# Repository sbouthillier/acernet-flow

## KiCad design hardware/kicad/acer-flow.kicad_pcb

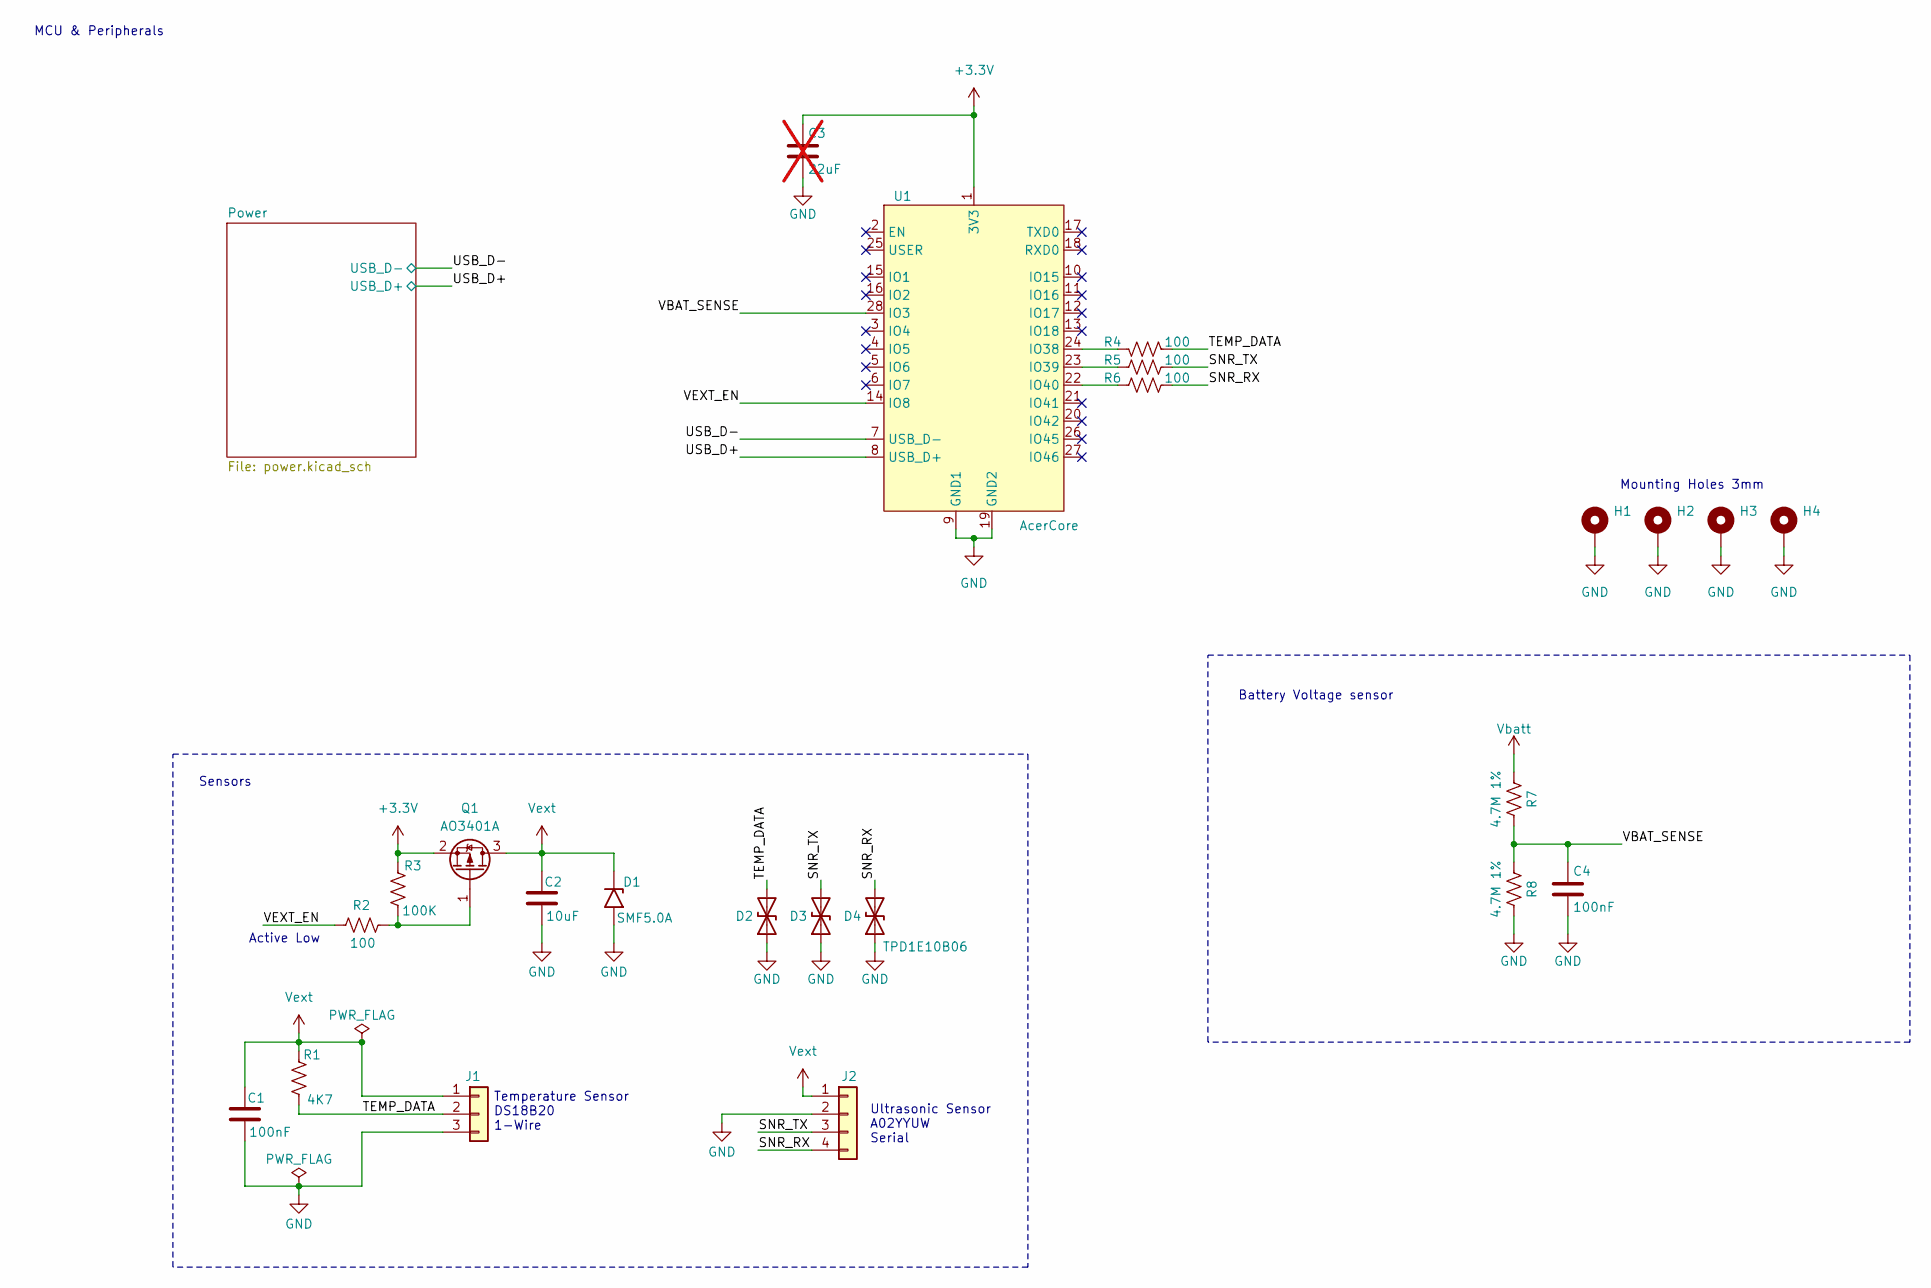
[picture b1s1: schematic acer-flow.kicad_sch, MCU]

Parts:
C1, C4: 100nF; C_0603_1608Metric; MPN CL10B104KB8WPNC
C2: 10uF; C_0603_1608Metric; MPN CL21A106KPFNNNG
C3: 22uF; C_0805_2012Metric; MPN CL21A226KPCLRNC; not fitted
D1: SMF5.0A; D_SOD-123F; MPN SMF5.0A
D2, D3, D4: TPD1E10B06; D_SOD-523; MPN TPD1E10B06DYAR
H1, H2, H3, H4: MountingHole_Pad; MountingHole_2.2mm_M2_ISO14580_Pad_TopBottom
J1: Conn_01x03; JST_XH_B3B-XH-A_1x03_P2.50mm_Vertical
J2: Conn_01x04; JST_XH_B4B-XH-A_1x04_P2.50mm_Vertical
Q1: AO3401A; SOT-23; MPN MMFTP3401-AQ
R1: 4K7; R_0603_1608Metric; MPN RC0603FR-074K7L
R2, R4, R5, R6: 100; R_0603_1608Metric; MPN RC0603FR-07100RL
R3: 100K; R_0603_1608Metric; MPN RC0603FR-07100KL
R7, R8: 4.7M 1%; R_0603_1608Metric; MPN RC0603FR-074M7L
U1: AcerCore

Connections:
+3.3V: C3.1, Q1.2 (S), R3.1, U1.1 (3V3); also elsewhere on the board
/SNR_RX: D4.2 (A2), J2.4, R6.2
/SNR_TX: D3.2 (A2), J2.3, R5.2
/TEMP_DATA: D2.2 (A2), J1.2, R1.2, R4.1
/USB_D+: U1.8 (USB_D+); also elsewhere on the board
/USB_D-: U1.7 (USB_D-); also elsewhere on the board
/VBAT_SENSE: C4.1, R7.2, R8.1, U1.28 (IO3)
/VEXT_EN: R2.1, U1.14 (IO8)
GND: C1.2, C2.2, C3.2, C4.2, D1.2 (A2), D2.1 (A1), D3.1 (A1), D4.1 (A1), H1.1 (1_1), H2.1 (1_1), H3.1 (1_1), H4.1 (1_1), J1.3, J2.2, R8.2, U1.9 (GND1), U1.19 (GND2); also elsewhere on the board
unnamed: Q1.1 (G), R2.2, R3.2
unnamed: R4.2, U1.24 (IO38)
unnamed: R5.1, U1.23 (IO39)
unnamed: R6.1, U1.22 (IO40)
Vbatt: R7.1; also elsewhere on the board
Vext: C1.1, C2.1, D1.1 (A1), J1.1, J2.1, Q1.3 (D), R1.1

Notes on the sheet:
Battery Voltage sensor
MCU & Peripherals
Mounting Holes 3mm
Active Low
Ultrasonic Sensor A02YYUW Serial
Sensors
Temperature Sensor DS18B20 1-Wire

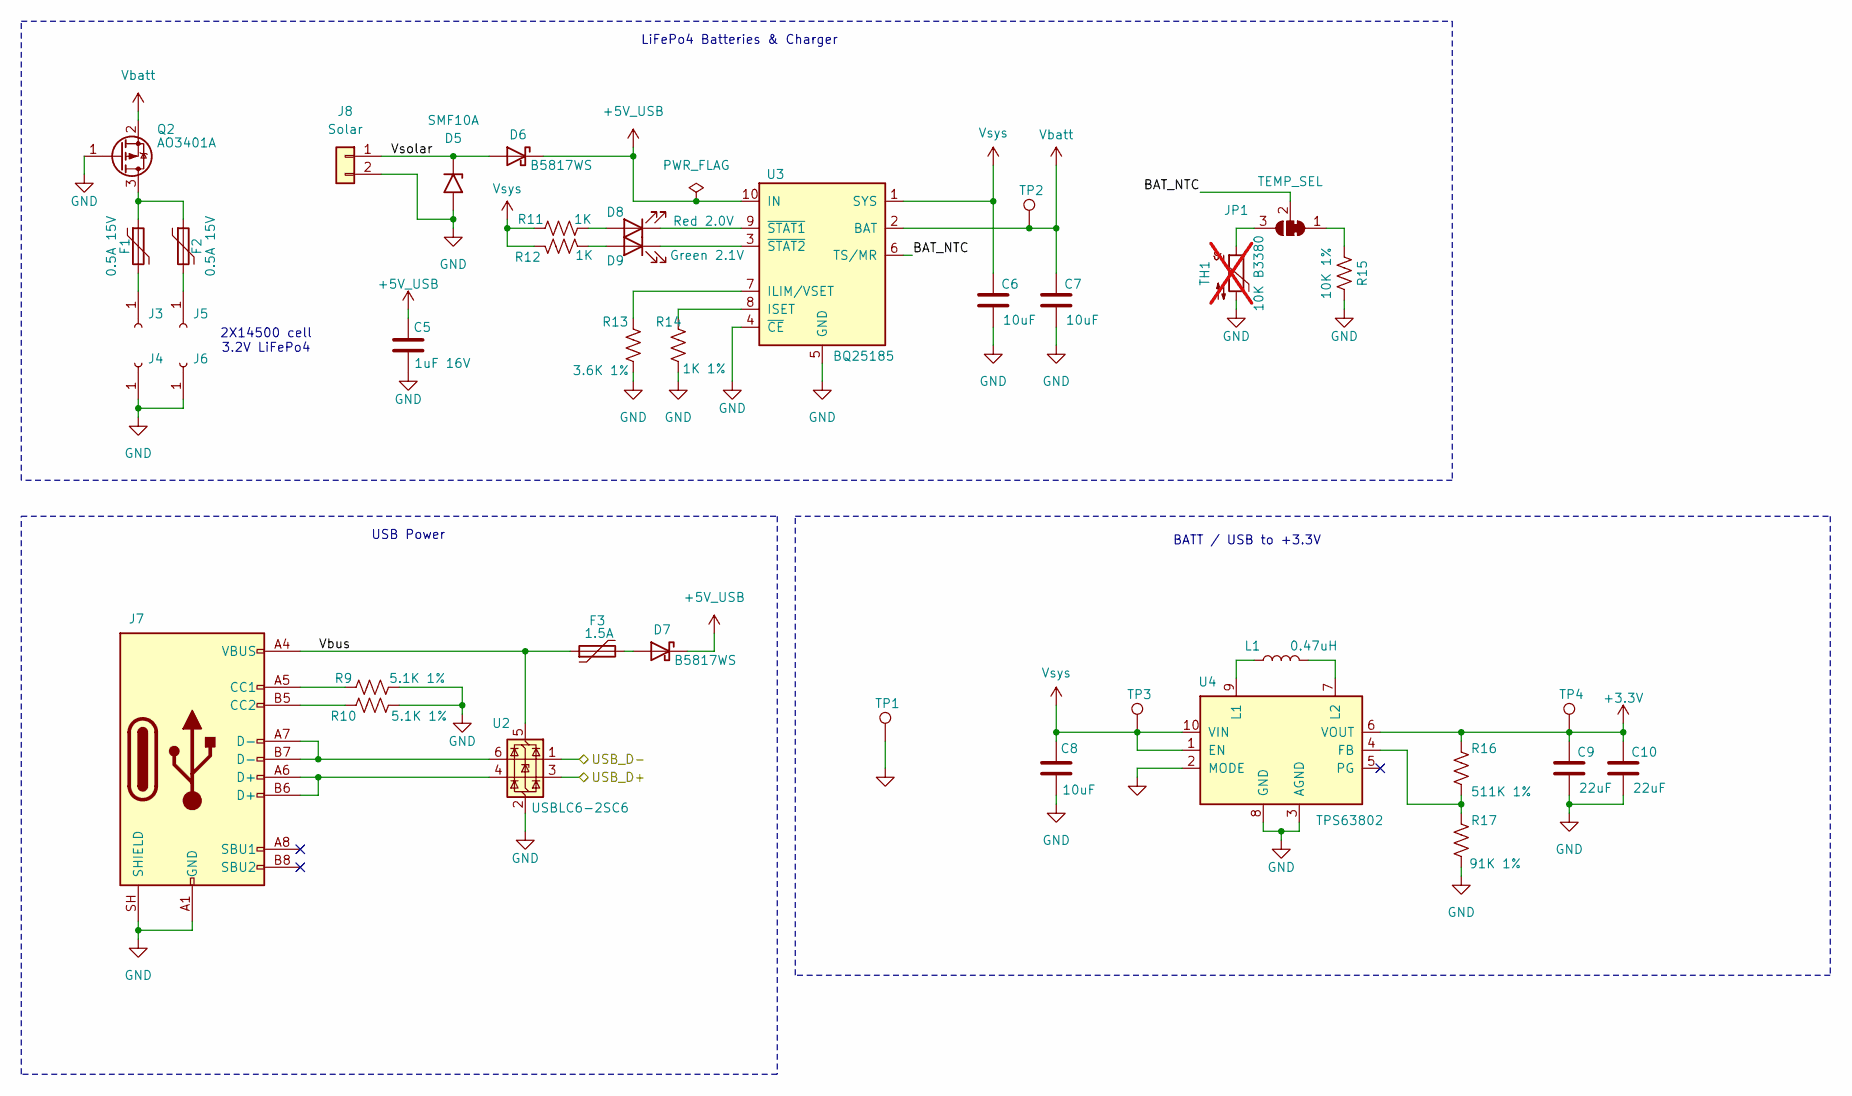
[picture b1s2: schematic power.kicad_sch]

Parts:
C5: 1uF 16V; C_0603_1608Metric; MPN CL10B105KO8VPNC
C6, C7, C8: 10uF; C_0603_1608Metric; MPN CL21A106KPFNNNG
C9, C10: 22uF; C_0805_2012Metric; MPN CL21A226KPCLRNC
D5: SMF10A; Nexperia_CFP3_SOD-123W; MPN SMF10A
D6, D7: B5817WS; D_SOD-323; MPN B5817WSHE3-TP
D8: Red 2.0V; LED_0603_1608Metric; MPN LTST-C190KRKT
D9: Green 2.1V; LED_0603_1608Metric; MPN LTST-C190GKT
F1, F2: 0.5A 15V; Fuse_1206_3216Metric; MPN 0ZCJ0050FF2G
F3: 1.5A; Fuse_1206_3216Metric; MPN 0ZCJ0150FF2C
J3, J4, J5, J6: Conn_01x01_Socket; BAT_BK-92; MPN BK-92
J7: USB_C_Receptacle_USB2.0_16P; UJ20-C-H-G-SMT-1-P16-TR; MPN UJ20-C-H-G-SMT-1-P16-TR
J8: Solar; JST_XH_B2B-XH-A_1x02_P2.50mm_Vertical
JP1: TEMP_SEL; SolderJumper-3_P1.3mm_Bridged12_RoundedPad1.0x1.5mm
L1: 0.47uH; L_Murata_DFE201610P; MPN DFE201612E-R47M=P2
Q2: AO3401A; SOT-23; MPN MMFTP3401-AQ
R9, R10: 5.1K 1%; R_0603_1608Metric; MPN RC0603FR-075K1L
R11, R12: 1K; R_0603_1608Metric; MPN RC0603FR-071KL
R13: 3.6K 1%; R_0603_1608Metric; MPN RC0603FR-073K6L
R14: 1K 1%; R_0603_1608Metric; MPN RC0603FR-071KL
R15: 10K 1%; R_0603_1608Metric; MPN RC0603FR-0710KL
R16: 511K 1%; R_0603_1608Metric; MPN RC0603FR-07511KL
R17: 91K 1%; R_0603_1608Metric; MPN RC0603FR-0791KL
TH1: 10K B3380; R_0603_1608Metric; MPN NCP18XH103F03RB; not fitted
TP1: GND; TestPoint_Pad_D1.5mm
TP2: Vbatt; TestPoint_Pad_D1.5mm
TP3: Vsys; TestPoint_Pad_D1.5mm
TP4: 3.3V; TestPoint_Pad_D1.5mm
U2: USBLC6-2SC6; SOT-23-6; MPN USBLC6-2SC6
U3: BQ25185; Texas_DLH0010A_WSON-10-1EP_2.2x2mm_P0.4mm_EP0.9x1.5mm_Therm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; MPN BQ25185DLHR
U4: TPS63802; VREG_TPS63802DLAR; MPN TPS63802DLAR

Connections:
+3.3V: C9.1, C10.1, R16.1, TP4.1, U4.6 (VOUT); also elsewhere on the board
+5V_USB: C5.1, D6.1 (K), D7.1 (K), U3.10 (IN)
/Power/BAT_NTC: JP1.2 (C), U3.6 (TS/MR)
/Power/Vbus: F3.1, J7.A4 (VBUS), J7.A9 (VBUS), J7.B4 (VBUS), J7.B9 (VBUS), U2.5 (VBUS)
/Power/Vsolar: D5.1 (A1), D6.2 (A), J8.1
/USB_D+: U2.3 (I/O2); also elsewhere on the board
/USB_D-: U2.1 (I/O1); also elsewhere on the board
GND: C5.2, C6.2, C7.2, C8.2, C9.2, C10.2, D5.2 (A2), J4.1 (Pin_1_1), J6.1 (Pin_1_1), J7.A1 (GND), J7.A12 (GND), J7.B1 (GND), J7.B12 (GND), J7.SH (SHIELD), J8.2, Q2.1 (G), R9.2, R10.2, R13.1, R14.2, R15.2, R17.2, TH1.2, TP1.1, U2.2 (GND), U3.4 (~CE), U3.5 (GND), U3.11 (EP), U4.2 (MODE), U4.3 (AGND), U4.8 (GND); also elsewhere on the board
unnamed: D7.2 (A), F3.2
unnamed: D8.2 (A), R11.2
unnamed: D8.1 (K), U3.9 (~STAT1)
unnamed: D9.2 (A), R12.2
unnamed: D9.1 (K), U3.3 (~STAT2)
unnamed: F1.2, J3.1 (Pin_1_1)
unnamed: F2.2, J5.1 (Pin_1_1)
unnamed: J7.A5 (CC1), R9.1
unnamed: J7.B5 (CC2), R10.1
unnamed: J7.A6 (D+), J7.B6 (D+), U2.4 (I/O2)
unnamed: J7.A7 (D-), J7.B7 (D-), U2.6 (I/O1)
unnamed: JP1.1 (A), R15.1
unnamed: JP1.3 (B), TH1.1
unnamed: F1.1, F2.1, Q2.3 (D)
unnamed: R13.2, U3.7 (ILIM/VSET)
unnamed: R14.1, U3.8 (ISET)
unnamed: R16.2, R17.1, U4.4 (FB)
unnamed: L1.1, U4.9 (L1)
unnamed: L1.2, U4.7 (L2)
Vbatt: C7.1, Q2.2 (S), TP2.1, U3.2 (BAT); also elsewhere on the board
Vsys: C6.1, C8.1, R11.1, R12.1, TP3.1, U3.1 (SYS), U4.1 (EN), U4.10 (VIN); also elsewhere on the board

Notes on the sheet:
BATT / USB to +3.3V
2X14500 cell 3.2V LiFePo4
LiFePo4 Batteries & Charger
USB Power

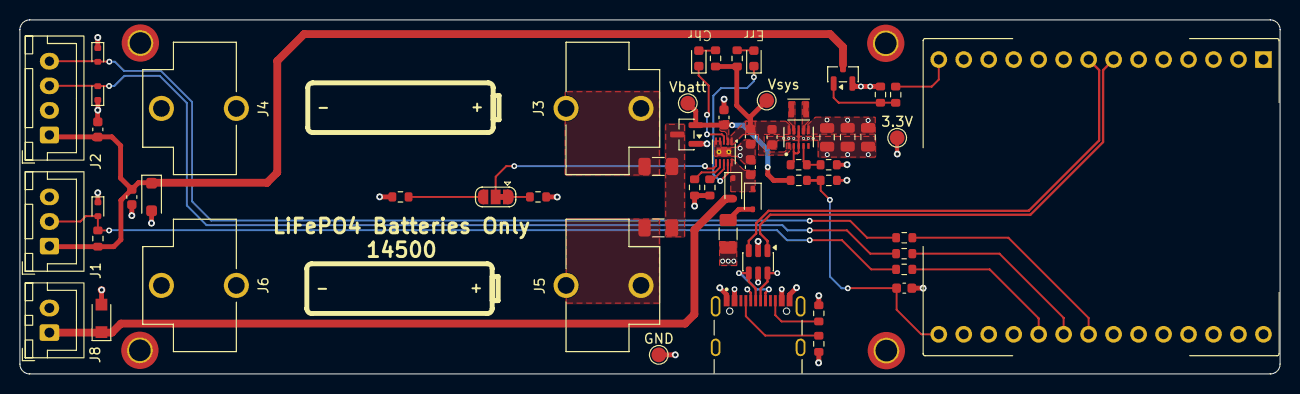
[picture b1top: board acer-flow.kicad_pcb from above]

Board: 4 copper layers, 128.1 x 36.0 mm, 64 parts (0 on the bottom side), 39 nets.

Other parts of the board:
3.3V: 3.3V; TestPoint_Pad_D1.5mm
GND: GND; TestPoint_Pad_D1.5mm
Vbatt: Vbatt; TestPoint_Pad_D1.5mm
Vsys: Vsys; TestPoint_Pad_D1.5mm

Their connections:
+3.3V: 3.3V.1 (1_1); also elsewhere on the board
GND: GND.1 (1_1); also elsewhere on the board
Vbatt: Vbatt.1 (1_1); also elsewhere on the board
Vsys: Vsys.1 (1_1); also elsewhere on the board

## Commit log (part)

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2026-06-23 Adding KiCad files
2026-06-25 Replacing MCU ESP32 by nRF54L15
2026-06-30 Adding footprints. Starting layout

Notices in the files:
hardware/kicad/acer-flow.kicad_pcb:
License CC BY-SA
